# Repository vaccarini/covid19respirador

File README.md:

# COVID19 Respirador
Repositorio de un respirador mecánico basado en recomendaciones médicas.

## Introducción
En progreso. Véase el documento: https://docs.google.com/document/d/1z06rEOX_Jf6soLEfomvGs7rINXRS_1dPuQfoMjTGBHs/edit?usp=sharing

## Motivación
La mayoría de los respiradores open source, no cubren los requerimientos médicos mínimos que se necesitan para tratar a un paciente que necesitan tratamiento para el coronavirus.

El diseño de un respirador que funcione y que permita cubrir la baja disponibilidad de los ventiladores UCI se hace imperante. 

Este proyecto intenta crear un ventilador que funcione para los casos indicados.

## Diagrama
En progreso. Véase el documento: https://docs.google.com/document/d/1z06rEOX_Jf6soLEfomvGs7rINXRS_1dPuQfoMjTGBHs/edit?usp=sharing

## Software
El sistema utilizará un módulo arduino. Se buscan colaboradores para el desarrollo y otros aspectos asociados.

## Contacto
Para integrarse al proyecto por favor contactarse con Martín Vaccarini en martin.vaccarini@gmail.com.

## Colaboración en repositorio
* Abrir un nuevo Issue, Forkear el proyecto o realizar un Pull Request.
* También se necesita ayuda en el documento del proyecto: https://docs.google.com/document/d/1z06rEOX_Jf6soLEfomvGs7rINXRS_1dPuQfoMjTGBHs/edit?usp=sharing

Colaboradores:
* Martín Vaccarini (autor) (@vaccarini)
* Ignacio Tolosa (asesor repositorio) (@itolosa)
* Mateo Roldan (alumno escuela Técnica 5)
* Gaston Calderon (alumno escuela técnica 5)
* Eduardo Hisch fábrica de PCB´s
* Javier Schwindt (donó sensor MAF) 
* Adrian Merlo (interlocutor para recibir donaciones)
* Martin ( impresos 3D)
* Nicolas Dumic (colabora teniendo otro proyecto en caminando)
* Walter van Derdonckt (argentina)
* Jon Ander Oribe (España)
* Guille Clave (argentina)
* Sebastian Padilla (españa)

* (Por completar)

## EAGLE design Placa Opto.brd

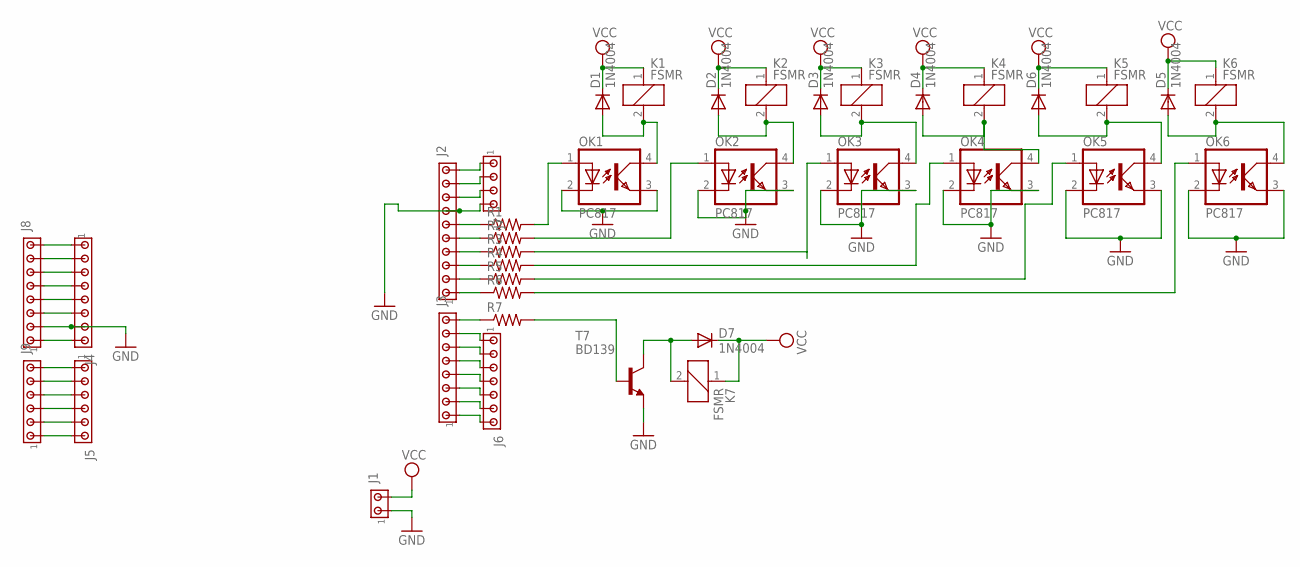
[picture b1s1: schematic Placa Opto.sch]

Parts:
D1, D2, D3, D4, D5, D6, D7: 1N4004; DO41-10
J1: MTA02-156; 1X2MTA
J2: MTA10-100; 10X10MTA
J3, J4, J8: MTA08-100; 10X08MTA
J5, J9: MTA06-100; 10X06MTA
J6: MTA07-100; 10X07MTA
J7: MTA04-100; 10X04MTA
K1, K2, K3, K4, K5, K6, K7: FSMR
OK1, OK2, OK3, OK4, OK5, OK6: PC817; DIL04
R1, R2, R3, R4, R5, R6, R7: R-US_0207/10; 0207/10
T7: BD139; TO126

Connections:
GND: J1.1, J2.7, J4.7, J7.4, J8.2, OK1.2 (C), OK1.3 (EMIT), OK2.2 (C), OK2.3 (EMIT), OK3.2 (C), OK3.3 (EMIT), OK4.2 (C), OK4.3 (EMIT), OK5.2 (C), OK5.3 (EMIT), OK6.2 (C), OK6.3 (EMIT), T7.1 (E)
unnamed: J2.1, R6.1
unnamed: J2.2, R5.1
unnamed: J2.3, R4.1
unnamed: J2.4, R3.1
unnamed: J2.5, R2.1
unnamed: J2.6, R1.1
unnamed: OK1.1 (A), R1.2
unnamed: D1.A, K1.2, OK1.4 (COL)
unnamed: OK2.1 (A), R2.2
unnamed: D2.A, K2.2, OK2.4 (COL)
unnamed: OK3.1 (A), R3.2
unnamed: D3.A, K3.2, OK3.4 (COL)
unnamed: OK4.1 (A), R4.2
unnamed: D4.A, K4.2, OK4.4 (COL)
unnamed: OK5.1 (A), R5.2
unnamed: OK6.1 (A), R6.2
unnamed: D5.A, K6.2, OK6.4 (COL)
unnamed: J3.8, R7.1
unnamed: R7.2, T7.3 (B)
unnamed: D7.A, K7.2, T7.2 (C)
unnamed: D6.A, K5.2, OK5.4 (COL)
unnamed: J3.7, J6.1
unnamed: J3.6, J6.2
unnamed: J3.5, J6.3
unnamed: J3.4, J6.4
unnamed: J3.3, J6.5
unnamed: J3.2, J6.6
unnamed: J3.1, J6.7
unnamed: J2.8, J7.3
unnamed: J2.9, J7.2
unnamed: J2.10, J7.1
unnamed: J4.1, J8.8
unnamed: J4.2, J8.7
unnamed: J4.3, J8.6
unnamed: J4.4, J8.5
unnamed: J4.5, J8.4
unnamed: J4.6, J8.3
unnamed: J4.8, J8.1
unnamed: J5.1, J9.6
unnamed: J5.2, J9.5
unnamed: J5.3, J9.4
unnamed: J5.4, J9.3
unnamed: J5.5, J9.2
unnamed: J5.6, J9.1
VCC: D1.C, D2.C, D3.C, D4.C, D5.C, D6.C, D7.C, J1.2, K1.1, K2.1, K3.1, K4.1, K5.1, K6.1, K7.1

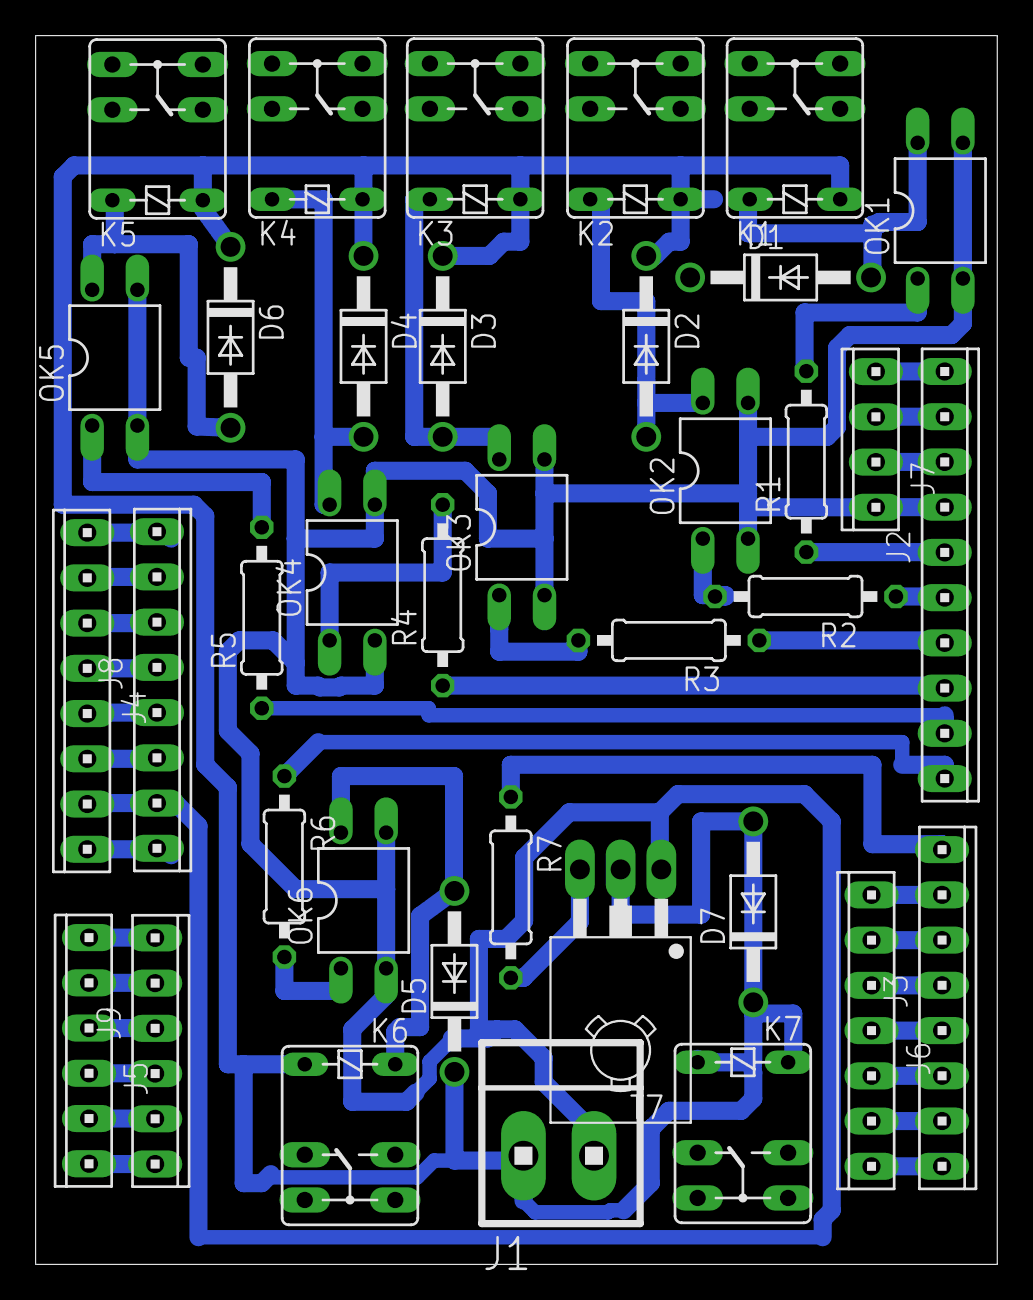
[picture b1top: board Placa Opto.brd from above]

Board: 2 copper layers, 54.0 x 69.0 mm, 37 parts (0 on the bottom side), 46 nets.

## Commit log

2020-03-26 Add initial files
2020-03-28 esquema respirador
    Esquema de respirador por inserción equipos de presión de aire y oxigeno
2020-03-29 Create Sensor_Ultrasonidos
2020-03-30 Create LICENSE
2020-03-30 Add files via upload
    Sensor volumetrico Diferencial Termico, mediante MDF vehiculo
2020-04-01 Placa PCB de arduino a placa encastre - comando etapa de potencia
    Por colaborativo de Gaston Calderon, quien diseño PC, para poder comandar las etapas de Solenoides (3), resistencias calorificas (1), pines libres arduino para Buzzer (1), Sensores barometricos (2), 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
2020-04-02 Diseño modelado del respirador
2020-04-02 Create PCB´s
    Archivos Download PCB EAGLE
2020-04-02 Create PCB
2020-04-11 Create Respirador_COV_19_Sensor_Dual_Ultrasonidos.ino
    Script for the dual ultrasonic sensor
2020-04-12 Create edit?usp=sharing
2020-04-12 Filtro Termico
    Se detalla la idea y lo que se fabrico
2020-04-12 Estructura de hierro
    Se comenta la idea y su fabricacion
